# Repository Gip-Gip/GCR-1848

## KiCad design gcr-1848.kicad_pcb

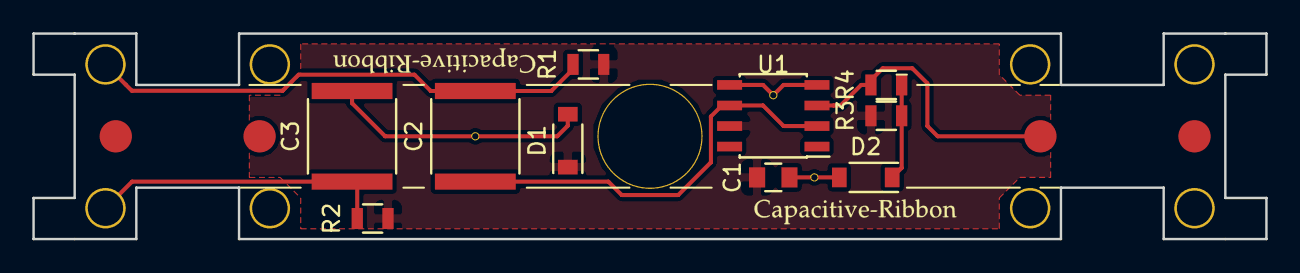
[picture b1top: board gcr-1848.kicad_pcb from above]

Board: 2 copper layers, 76.2 x 12.7 mm, 10 parts (0 on the bottom side), 7 nets.

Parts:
C1: C_0805
C2, C3: C_2220
D1: 24V; SOD-123
D2: SOD-123
R1, R2, R3, R4: R_0805
U1: SOIC-8_3.9x4.9mm_Pitch1.27mm

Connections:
+24V: C1.2, D1.1, R1.1, R2.1, R3.1, U1.7
Earth: C1.1, C3.2, D1.2, D2.2, U1.4, U1.5
unnamed: C2.1, R1.2
unnamed: C2.2, U1.2, U1.6
unnamed: C3.1, R2.2
unnamed: R4.2, U1.3
unnamed: D2.1, R3.2, R4.1

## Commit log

2018-07-12 Created first revision of schematic
2018-07-12 Annotated some components and added a few Greek letters
2018-07-14 Laid out components on PCB
2018-07-14 Updated gerbers and board design
2018-07-14 Added OSHPark renditions of the PCB layers
2018-07-16 Updated PCB and rearranged schematic
